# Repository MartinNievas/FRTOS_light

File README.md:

# Linterna frontal con diferentes modos de iluminación
La linterna cuenta con diferentes modos de iluminación. Es una versión simplificada inspirada en el modelo 
[NAO&reg;](https://www.petzl.com/US/en/Sport/PERFORMANCE-headlamps/NAO) de Petzl&reg;

## Modos de iluminación
* OFF (Default)
* ADAPTABLE
* AMPLIO
* CENTRADO
* AMPLIO + CENTRADO

##### Modo ADAPTABLE
La linterna regula la intensidad de los LED basada en la medición realizada por un fotodiodo. Los umbrales de cambio 
de intensidad controlan una máquina de estados, para evitar oscilaciones al cambiar entre modos.

## Circuito
La linterna se controla mediante una Arduino Pro-Mini y dos mosfet SMD (si2302) para controlar los LED. Cuenta con un botón en la placa 
para ir cambiando entre modos. 

## Alimentación
Utiliza dos bateras 18650 en serie. Esto  es así para alimentar la Arduino mediante el regulador provisto en la placa. 

## LEDs
La linterna utiliza dos LED. Uno de 3W para la iluminación centrada con un colimador de 16°, y un led de 5W para 
la iluminación amplia con un difusor de 60°

## Compilación y carga
El proyecto utiliza [platformio](http://platformio.org/). Para compilar y cargar en la Arduino hacer:
```
platofrmio run -t upload
```

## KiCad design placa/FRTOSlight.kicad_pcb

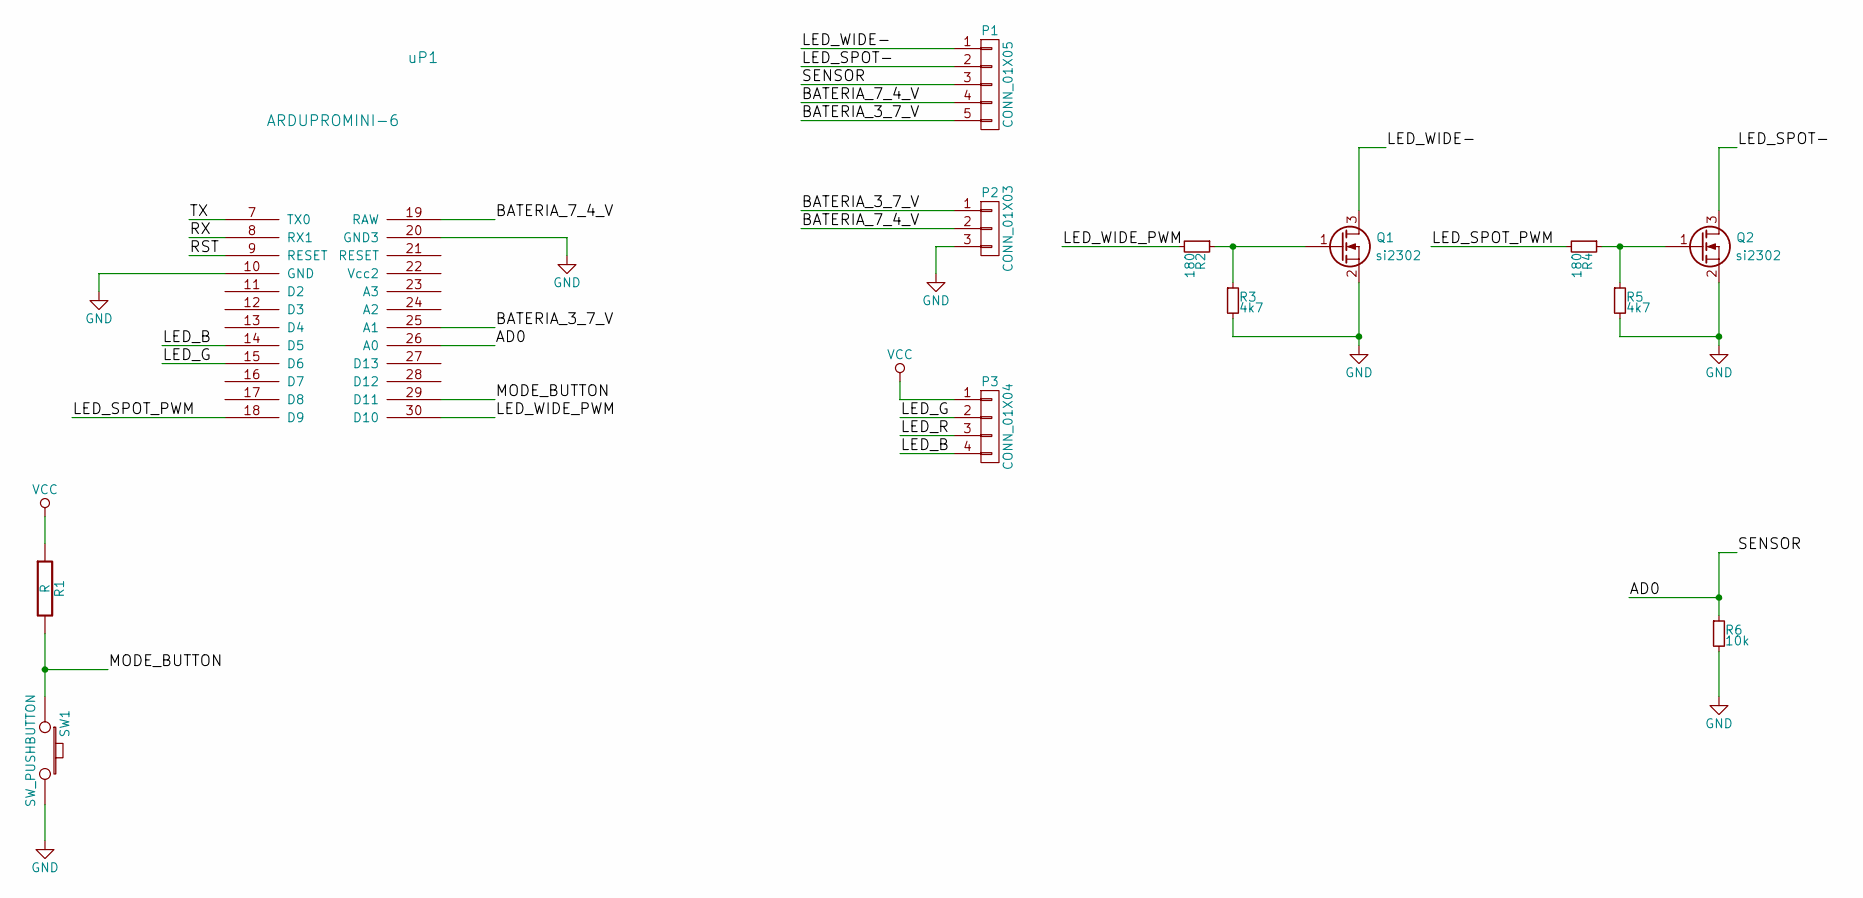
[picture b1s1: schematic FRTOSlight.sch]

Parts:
P1: CONN_01X05; 1X05
P2: CONN_01X03; 1X03
P3: CONN_01X04; 1X04
Q1, Q2: si2302; SOT23-3
R1: R; 1206
R2, R4: 180; 0805
R3, R5: 4k7; 1206
R6: 10k; 1206
SW1: SW_PUSHBUTTON; SW_PUSHBUTTON_PTH
uP1: ARDUPROMINI-6; ArduProMini-6

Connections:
/AD0: P1.3, R6.1, uP1.26 (A0)
/BATERIA_3_7_V: P1.5, P2.1, uP1.25 (A1)
/BATERIA_7_4_V: P1.4, P2.2, uP1.19 (RAW)
/LED_B: P3.4, uP1.14 (D5)
/LED_G: P3.2, uP1.15 (D6)
/LED_R: P3.3
/LED_SPOT-: P1.2, Q2.3 (D)
/LED_SPOT_PWM: R4.2, uP1.18 (D9)
/LED_WIDE-: P1.1, Q1.3 (D)
/LED_WIDE_PWM: R2.2, uP1.30 (D10)
/MODE_BUTTON: R1.2, SW1.1, uP1.29 (D11)
/RST: uP1.9 (RESET)
/RX: uP1.8 (RX1)
/TX: uP1.7 (TX0)
GND: P2.3, Q1.2 (S), Q2.2 (S), R3.2, R5.2, R6.2, SW1.2, uP1.10 (GND), uP1.20 (GND3)
unnamed: Q1.1 (G), R2.1, R3.1
unnamed: Q2.1 (G), R4.1, R5.1
VCC: P3.1, R1.1

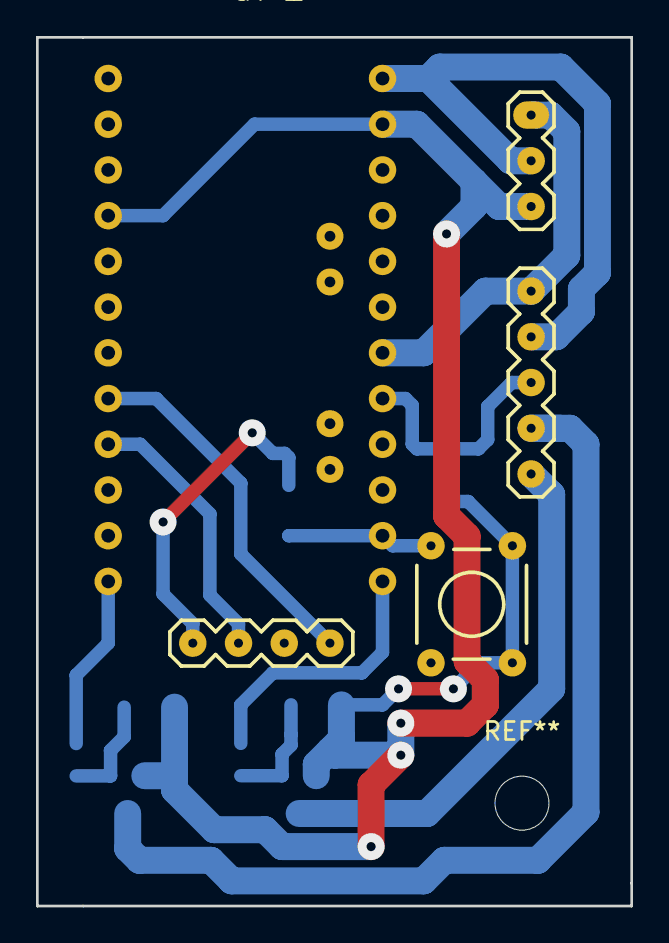
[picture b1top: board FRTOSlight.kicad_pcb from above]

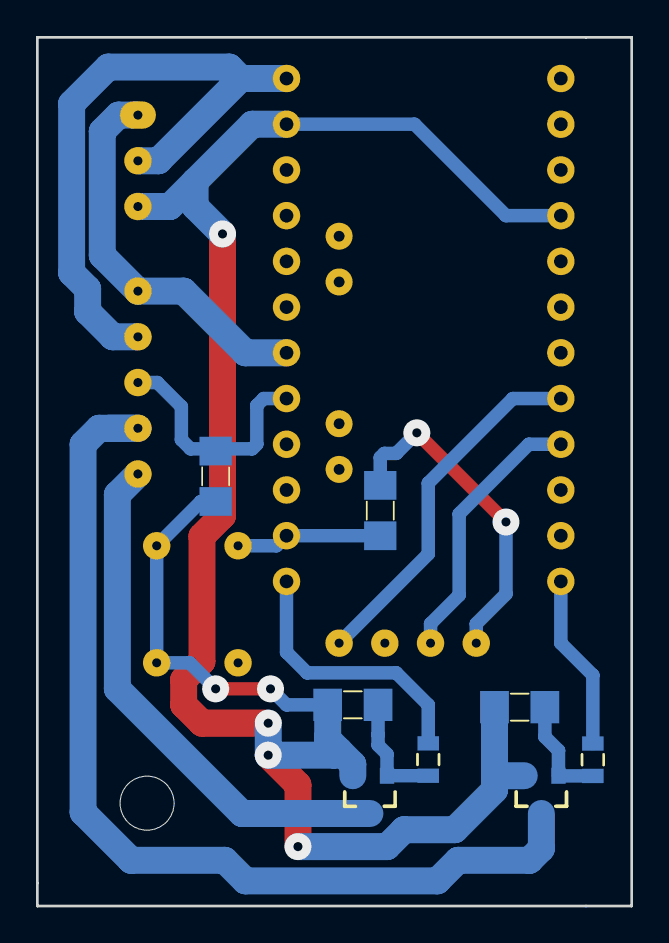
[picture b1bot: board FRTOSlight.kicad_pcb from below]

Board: 2 copper layers, 33.0 x 48.3 mm, 13 parts (8 on the bottom side), 14 nets.

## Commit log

2017-11-22 Boton para cambiar de modo funcionando Intensidad de la linterna cambia con la luz ambiente
2017-11-22 limpieza
2017-11-25 Versión 0.1 de la carcasa. Cuando la imprimí le faltó un poco mas de altura para que quedara bien el colimador, habría que calibrarlo para cada versión :\
2017-11-25 Función para el blink en rGB
2017-11-25 Blink BREATH funcionando. El led que tengo es anodo común, por eso está invertido el ciclo de PWM
2017-11-27 Carcasa posterior. Dos partes, el porta baterías y la tapa
2017-11-27 PCB para la arduino pro mini con los driver de los LEDs y el botón incluido
2017-11-27 Función de realimentación de la intensidad lumínica frontal, con un filtro pasabajos incluído para que los cambios no sean tan abruptos
2017-11-29 Modificaciones en el botón de cambio de modo
2017-12-02 Configuración para el modo de iluminación automático
2017-12-02 Ordenando el código. Versión 1.0 estable
2017-12-02 Creación del README
2017-12-06 Licencia

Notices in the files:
README.md:
License: CC BY-SA 4.0
